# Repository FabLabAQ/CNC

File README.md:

# CNC

Migliorie da apportare alla CNC

[Lista della spesa](https://docs.google.com/spreadsheets/d/1Wq6bE2mLNkH-loEp1lNx39WeWIYjqB_c8ai0cWjN81c/edit?usp=sharing)

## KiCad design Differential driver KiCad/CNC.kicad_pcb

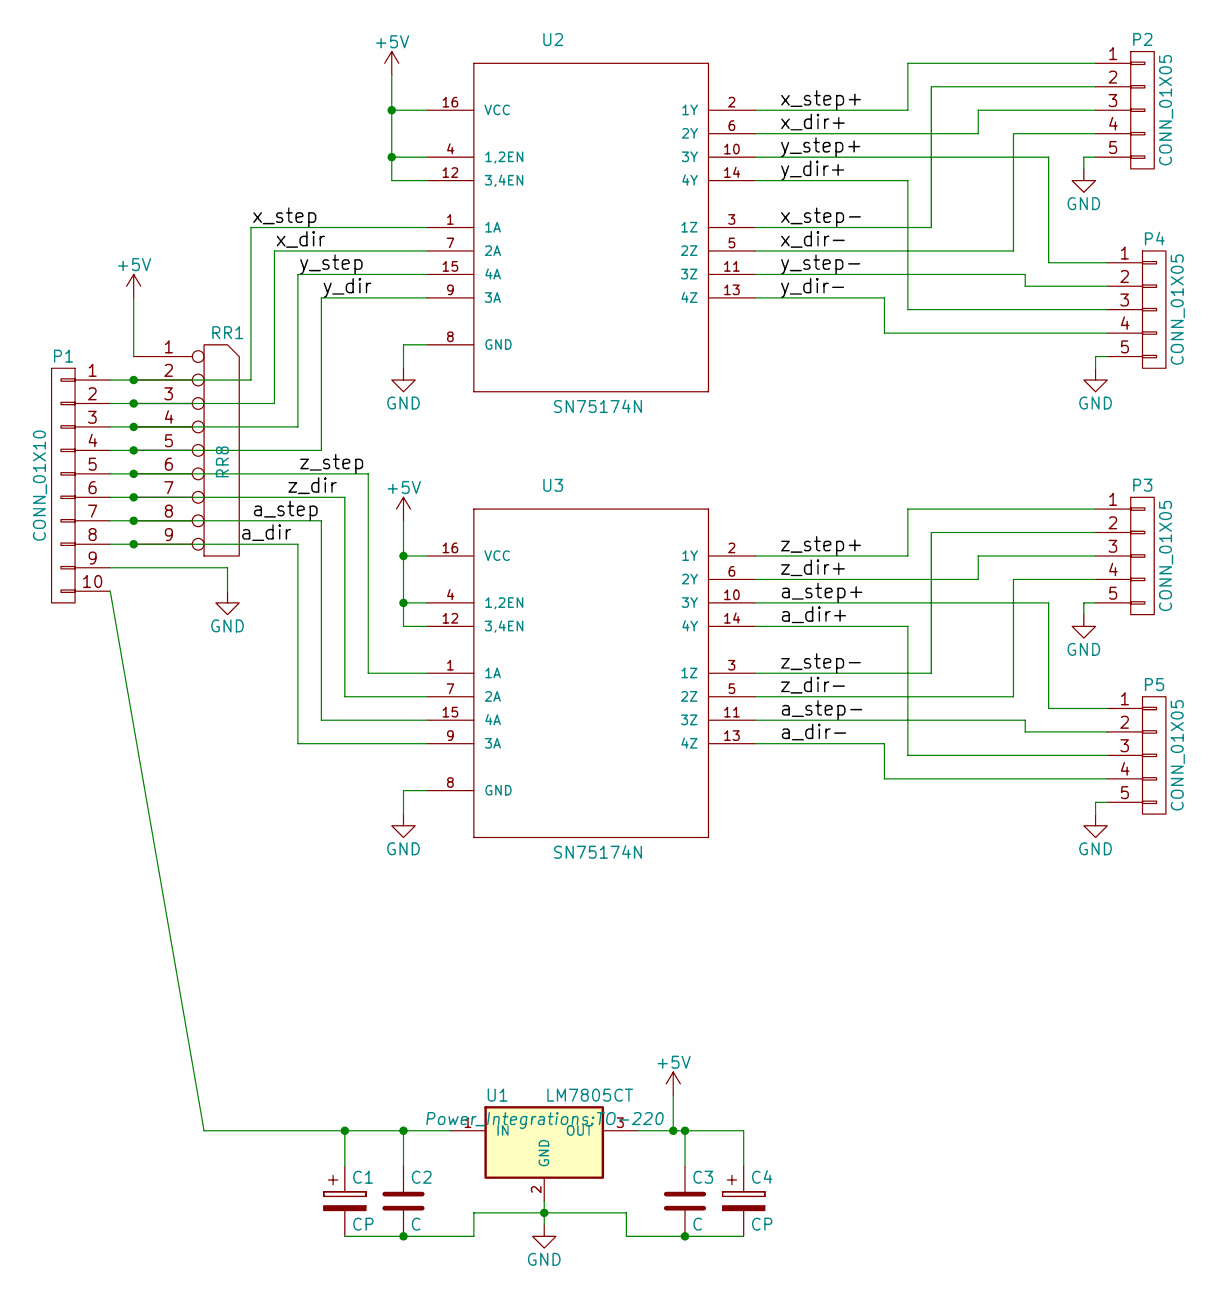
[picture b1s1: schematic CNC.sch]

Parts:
C1, C4: CP; C_Radial_D5_L6_P2.5
C2, C3: C; C_Disc_D3_P2.5
P1: CONN_01X10; TerminalBlock_Pheonix_MKDS1.5-10pol
P2, P3, P4, P5: CONN_01X05; TerminalBlock_Pheonix_MKDS1.5-5pol
RR1: RR8; Resistor_Array_SIP8
U1: LM7805CT; TO-220
U2, U3: SN75174N; DIP-16_W7.62mm_LongPads

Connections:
+5V: C3.1, C4.1, RR1.1 (COM), U1.3 (OUT), U2.4 (1,2EN), U2.12 (3,4EN), U2.16 (VCC), U3.4 (1,2EN), U3.12 (3,4EN), U3.16 (VCC)
/a_dir: P1.8, RR1.9, U3.9 (3A)
/a_dir+: P5.3, U3.14 (4Y)
/a_dir-: P5.4, U3.13 (4Z)
/a_step: P1.7, RR1.8, U3.15 (4A)
/a_step+: P5.1, U3.10 (3Y)
/a_step-: P5.2, U3.11 (3Z)
/x_dir: P1.2, RR1.3, U2.7 (2A)
/x_dir+: P2.3, U2.6 (2Y)
/x_dir-: P2.4, U2.5 (2Z)
/x_step: P1.1, RR1.2, U2.1 (1A)
/x_step+: P2.1, U2.2 (1Y)
/x_step-: P2.2, U2.3 (1Z)
/y_dir: P1.4, RR1.5, U2.9 (3A)
/y_dir+: P4.3, U2.14 (4Y)
/y_dir-: P4.4, U2.13 (4Z)
/y_step: P1.3, RR1.4, U2.15 (4A)
/y_step+: P4.1, U2.10 (3Y)
/y_step-: P4.2, U2.11 (3Z)
/z_dir: P1.6, RR1.7, U3.7 (2A)
/z_dir+: P3.3, U3.6 (2Y)
/z_dir-: P3.4, U3.5 (2Z)
/z_step: P1.5, RR1.6, U3.1 (1A)
/z_step+: P3.1, U3.2 (1Y)
/z_step-: P3.2, U3.3 (1Z)
GND: C1.2, C2.2, C3.2, C4.2, P1.9, P2.5, P3.5, P4.5, P5.5, U1.2 (GND), U2.8 (GND), U3.8 (GND)
unnamed: C1.1, C2.1, P1.10, U1.1 (IN)

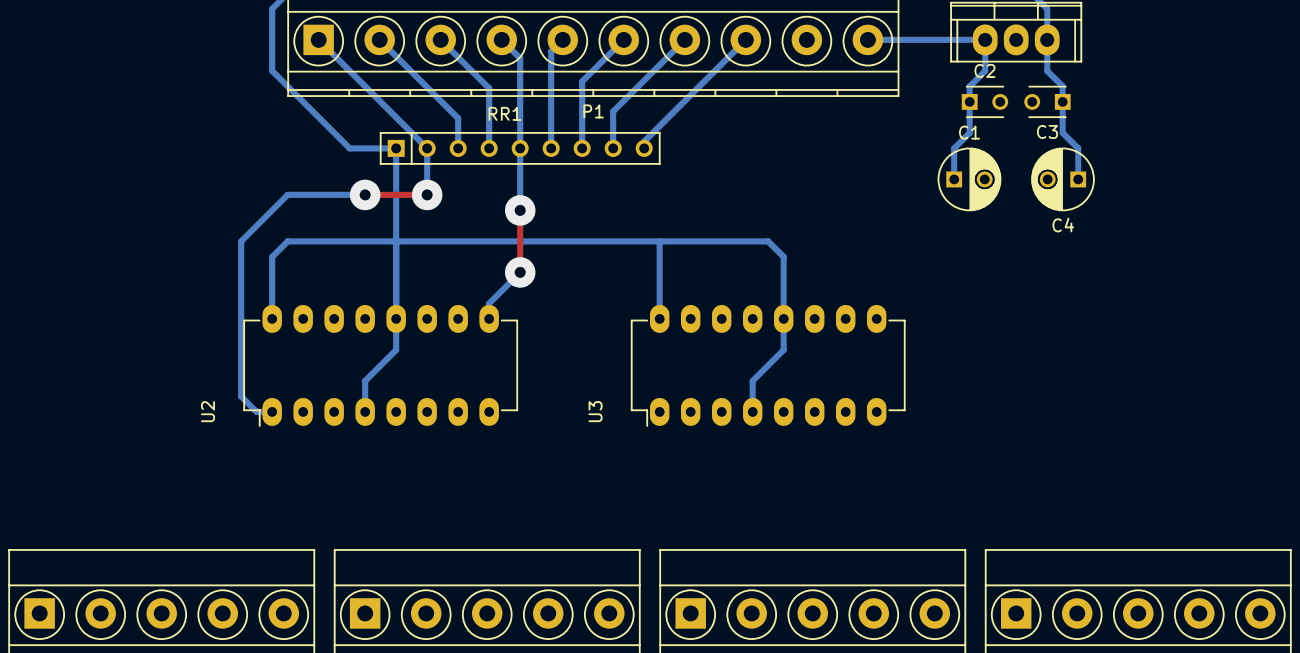
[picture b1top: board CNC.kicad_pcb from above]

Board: 2 copper layers, 13 parts (0 on the bottom side), 27 nets.

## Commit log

2017-01-28 new docs
2017-02-05 differetial driver
2017-02-06 started electronics box
2017-02-07 driver update
2017-02-11 new driver version
2017-03-23 add A-axis servo
2017-07-05 conn panel
2017-07-25 handWheel
2017-07-26 back panel
